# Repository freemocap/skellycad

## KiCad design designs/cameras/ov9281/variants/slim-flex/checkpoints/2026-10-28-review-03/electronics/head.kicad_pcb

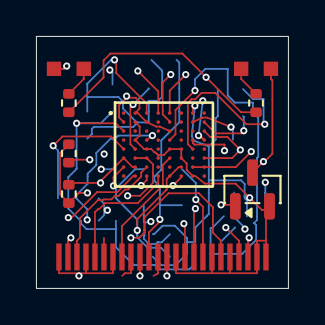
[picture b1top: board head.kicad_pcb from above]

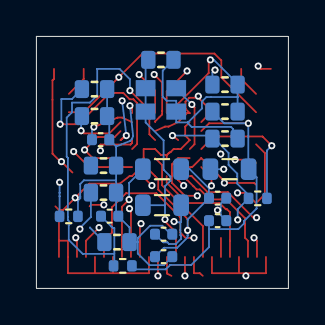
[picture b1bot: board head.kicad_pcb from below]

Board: 4 copper layers, 14.0 x 14.0 mm, 31 parts (22 on the bottom side), 30 nets.

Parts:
C7, C8, C10, C12, C13, C18, C19, C21, C33: C_1u_0603; C_0603_1608Metric
C9, C14, C15, C16, C17, C20: C_100n_6V3_0402; C_0402_1005Metric
D201, D202: AP1608F3C; Kingbright_AP1608F3C_R09
J201: SOLDER FLEX / 24 contacts; Flex_Solder_24_P0.5_R05
L1, L2, L3: MLP2012S3R3MT; L_0805_2012Metric
Q201: MMBT3904,215; SOT-23
R7, R8, R9: R_0R_0402; R_0402_1005Metric
R201, R202: 1k 1%; R_0402_1005Metric
R203: 2.2k 1%; R_0402_1005Metric
R204: 100k 1%; R_0402_1005Metric
U1: ImageSensor_OV9281; OV9281
Y1: SG-210STF 24.0000ML; Epson_SG210STF_2.5x2.0mm_R09

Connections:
+1V2: J201.17, L1.1
+1V8: C33.1, J201.11, L2.1, Y1.1, Y1.4
+2V8: J201.19, L3.1
+3V3: J201.21, R201.1, R202.1
/CAM_L_CLK_N: J201.5, U1.H4
/CAM_L_CLK_P: J201.6, U1.G4
/CAM_L_D0_N: J201.2, U1.H3
/CAM_L_D0_P: J201.3, U1.G3
/CAM_L_D1_N: J201.8, U1.F5
/CAM_L_D1_P: J201.9, U1.G5
/CAM_NRST_1V8: J201.15, U1.A5
/IR_A1: D201.2, R201.2
/IR_A2: D202.2, R202.2
/IR_BASE: Q201.1, R203.2, R204.1
/IR_K: D201.1, D202.1, Q201.3
/LED_PWM: J201.22, R203.1
/M1_AVDD: C18.1, C19.1, C20.1, L3.2, R9.2, U1.B8, U1.C1, U1.G7, U1.G8
/M1_CAM_SCL_1V8: J201.12, U1.E4
/M1_CAM_SDA_1V8: J201.13, U1.A4
/M1_DOVDD: C13.1, C15.1, C16.1, L2.2, R7.1, U1.B7, U1.D3, U1.H2, U1.H6
/M1_DVDD: C9.1, C12.1, C14.1, L1.2, U1.A2, U1.B1, U1.B3, U1.C5, U1.D8, U1.F2, U1.F3, U1.G1, U1.G6, U1.H5
/M1_MCLK: U1.E2, Y1.3
/M1_PVDD: C17.1, R9.1, U1.D5
/M1_SID: R7.2, R8.1, U1.E1
/M1_VH: C21.1, U1.E8
/M1_VN1: C7.1, U1.D7
/M1_VN2: C8.1, U1.E7
/M1_VN3: C10.1, U1.F7
/M1_VSYNC_1V8_M: J201.16, U1.B5
GND: C7.2, C8.2, C9.2, C10.2, C12.2, C13.2, C14.2, C15.2, C16.2, C17.2, C18.2, C19.2, C20.2, C21.2, C33.2, J201.1, J201.4, J201.7, J201.10, J201.14, J201.18, J201.20, J201.23, J201.24, Q201.2, R8.2, R204.2, U1.A3, U1.A7, U1.B2, U1.C8, U1.D2, U1.E3, U1.E5, U1.E6, U1.F1, U1.F4, U1.F6, U1.F8, U1.G2, U1.H7, Y1.2

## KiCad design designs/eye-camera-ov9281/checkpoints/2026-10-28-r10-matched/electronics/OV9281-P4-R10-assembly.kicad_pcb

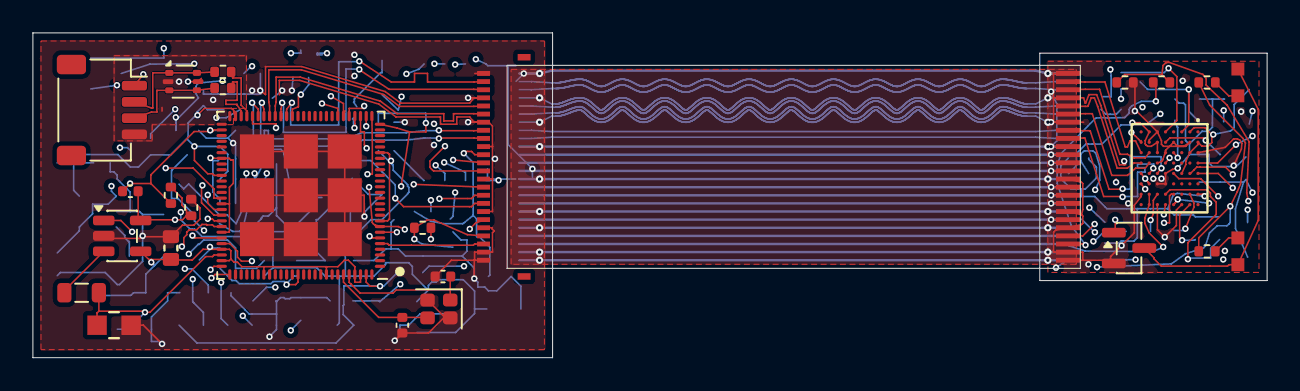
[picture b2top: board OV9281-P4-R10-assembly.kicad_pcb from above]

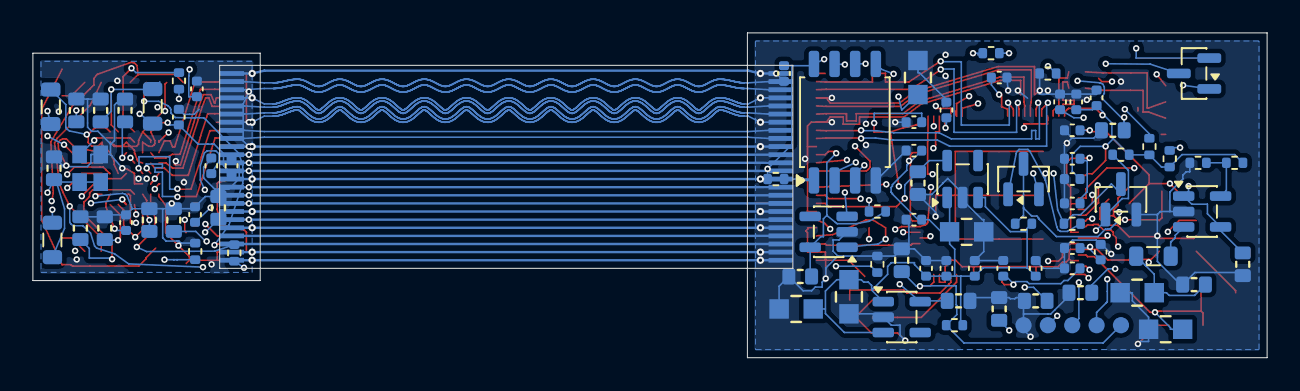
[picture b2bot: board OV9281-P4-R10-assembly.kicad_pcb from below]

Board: 6 copper layers, 76.0 x 20.0 mm, 110 parts (84 on the bottom side), 62 nets.

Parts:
C1, C2, C3: C_4u7_0805; C_0805_2012Metric
C4, C5, C6, C7, C8, C10, C12, C13, C18, C19, C21, C33: C_1u_0603; C_0603_1608Metric
C9, C14, C15, C16, C17, C20: C_100n_6V3_0402; C_0402_1005Metric
C101, C102: CL_TBD; C_0402_1005Metric
C103, C132, C135: 100n; C_0402_1005Metric
C104, C125, C126, C127, C133: 1u; C_0603_1608Metric
C105, C108, C136: 4.7u; C_0603_1608Metric
C106, C109: 22u; C_0805_2012Metric
C107: 22p; C_0402_1005Metric
C110: 100n / U101.9; C_0402_1005Metric
C111: 100n / U101.21; C_0402_1005Metric
C112: 100n / U101.26; C_0402_1005Metric
C113: 100n / U101.54; C_0402_1005Metric
C114: 100n / U101.62; C_0402_1005Metric
C115: 100n / U101.75; C_0402_1005Metric
C116: 100n / U101.76; C_0402_1005Metric
C117: 100n / U101.77; C_0402_1005Metric
C118: 100n / U101.85; C_0402_1005Metric
C119: 100n / U101.91; C_0402_1005Metric
C120: 100n / U101.96; C_0402_1005Metric
C121: 100n / U101.101; C_0402_1005Metric
C122: 100n / U101.102; C_0402_1005Metric
C123, C124: 10u; C_0805_2012Metric
C128: 100n / U101.30; C_0402_1005Metric
C129: 100n / U101.59; C_0402_1005Metric
C130: 100n / U101.67; C_0402_1005Metric
C131, C134: 10n; C_0402_1005Metric
D201, D202: AP1608F3C; Kingbright_AP1608F3C_R09
J101: USB / JST 4-contact candidate; JST_SH_SM04B-SRSS-TB_1x04-1MP_P1.00mm_Horizontal
J102: FH34SRJ-24S-0.5SH(99); Hirose_FH34SRJ_24S_0.5SH_R05
J103: PROGRAM / RESET pads; ProgrammingPads_5x1mm_P1.5mm
J201: SOLDER FLEX / 24 contacts; Flex_Solder_24_P0.5_R05
J301, J302: FLEX CONTACTS / B.Cu; Flex_Contacts_R05
L1, L2, L3: MLP2012S3R3MT; L_0805_2012Metric
L101, L102: 2.2u / Isat TBD; L_0805_2012Metric
Q101, Q102: BSS138; SOT-23
Q103: BSS138 / reset asserted HIGH; SOT-23
Q201: MMBT3904,215; SOT-23
R7, R8, R9: R_0R_0402; R_0402_1005Metric
R101, R102, R103, R104, R117, R118: 10k; R_0402_1005Metric
R105, R106: 499k; R_0402_1005Metric
R107: 453k; R_0402_1005Metric
R108, R116: 100k; R_0402_1005Metric
R109, R110: 0; R_0402_1005Metric
R111: 4.02k 1%; R_0402_1005Metric
R112, R113, R114, R115: 4.7k; R_0402_1005Metric
R201, R202: 1k 1%; R_0402_1005Metric
R203: 2.2k 1%; R_0402_1005Metric
R204: 100k 1%; R_0402_1005Metric
U1: ImageSensor_OV9281; OV9281
U5: TLV73318PDBVT; SOT-23-5
U6: TLV73312PDBVT; SOT-23-5
U7: TLV73328PDBVT; SOT-23-5
U101: ESP32-P4NRW16X / v3.x; ESP32-P4
U102: W25Q32JVSS (4 MB candidate); SOIC-8_5.3x5.3mm_P1.27mm
U103: TLV62569DBV / core; SOT-23-5
U104: TLV62569DBV / system; SOT-23-5
U105: USBLC6-2P6; SOT-666
Y1: SG-210STF 24.0000ML; Epson_SG210STF_2.5x2.0mm_R09
Y101: 40 MHz / CL TBD; Crystal_SMD_2016-4Pin_2.0x1.6mm

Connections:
+1V2: C6.1, J102.17, J201.17, J301.17, J302.17, L1.1, U6.5
+1V8: C5.1, C33.1, J102.11, J201.11, J301.11, J302.11, L2.1, Q101.1, Q102.1, R112.1, R114.1, R117.1, U5.5, Y1.1, Y1.4
+2V8: C4.1, J102.19, J201.19, J301.19, J302.19, L3.1, U7.5
+3V3: C1.1, C2.1, C3.1, C105.1, C109.1, C110.1, C111.1, C114.1, C115.1, C117.1, C118.1, C120.1, C121.1, C122.1, C123.1, C134.1, C135.1, C136.1, J102.21, J201.21, J301.21, J302.21, L102.2, R102.1, R103.1, R104.1, R107.1, R113.1, R115.1, R116.1, R201.1, R202.1, U5.1, U5.3, U6.1, U6.3, U7.1, U7.3, U101.9, U101.21, U101.51, U101.62, U101.75, U101.77, U101.85, U101.96, U101.101, U101.102, U103.4
/CAM_L_CLK_N: J102.5, J201.5, J301.5, J302.5, U1.H4, U101.45
/CAM_L_CLK_P: J102.6, J201.6, J301.6, J302.6, U1.G4, U101.44
/CAM_L_D0_N: J102.2, J201.2, J301.2, J302.2, U1.H3, U101.42
/CAM_L_D0_P: J102.3, J201.3, J301.3, J302.3, U1.G3, U101.43
/CAM_L_D1_N: J102.8, J201.8, J301.8, J302.8, U1.F5, U101.46
/CAM_L_D1_P: J102.9, J201.9, J301.9, J302.9, U1.G5, U101.47
/CAM_NRST_1V8: J102.15, J201.15, J301.15, J302.15, Q103.3, R117.2, U1.A5
/CAM_RESET_ASSERT: Q103.1, R116.2, U101.6
/CAM_SCL_3V3: Q101.3, R113.2, U101.7
/CAM_SDA_3V3: Q102.3, R115.2, U101.8
/FLASH_CLK: U101.32, U102.6
/FLASH_CS: R101.2, U101.27, U102.1
/FLASH_D: U101.33, U102.5
/FLASH_HOLD: U101.31, U102.7
/FLASH_Q: U101.28, U102.2
/FLASH_WP: U101.29, U102.3
/IR_A1: D201.2, R201.2
/IR_A2: D202.2, R202.2
/IR_BASE: Q201.1, R203.2, R204.1
/IR_K: D201.1, D202.1, Q201.3
/LED_PWM: J102.22, J201.22, J301.22, J302.22, R203.1, U101.5
/M1_AVDD: C18.1, C19.1, C20.1, L3.2, R9.2, U1.B8, U1.C1, U1.G7, U1.G8
/M1_CAM_SCL_1V8: J102.12, J201.12, J301.12, J302.12, Q101.2, R112.2, U1.E4
/M1_CAM_SDA_1V8: J102.13, J201.13, J301.13, J302.13, Q102.2, R114.2, U1.A4
/M1_DOVDD: C13.1, C15.1, C16.1, L2.2, R7.1, U1.B7, U1.D3, U1.H2, U1.H6
/M1_DVDD: C9.1, C12.1, C14.1, L1.2, U1.A2, U1.B1, U1.B3, U1.C5, U1.D8, U1.F2, U1.F3, U1.G1, U1.G6, U1.H5
/M1_MCLK: U1.E2, Y1.3
/M1_PVDD: C17.1, R9.1, U1.D5
/M1_SID: R7.2, R8.1, U1.E1
/M1_VH: C21.1, U1.E8
/M1_VN1: C7.1, U1.D7
/M1_VN2: C8.1, U1.E7
/M1_VN3: C10.1, U1.F7
/M1_VSYNC_1V8_M: J102.16, J201.16, J301.16, J302.16, R118.1, U1.B5
/P4_BOOT: J103.4, R103.2, U101.66
/P4_CSI_REXT: R111.1, U101.48
/P4_DOWNLOAD_ENABLE: R104.2, U101.68
/P4_EN: C104.1, J103.5, R102.2, U101.103
/P4_EN_DCDC: U101.79, U103.1
/P4_FB: C107.2, R105.2, R106.1, U101.78, U103.5
/P4_FLASH_VDD: C103.1, C125.1, C128.1, R101.1, U101.30, U101.71, U102.8
/P4_LDO4_UNUSED: C127.1, U101.74
/P4_MIPI_2V5: C131.1, C132.1, C133.1, U101.41, U101.73
/P4_PSRAM_VDD: C126.1, C129.1, C130.1, U101.59, U101.67, U101.72
/P4_SW: L101.1, U103.3
/P4_UART_RX: J103.3, U101.70
/P4_UART_TX: J103.2, U101.69
/P4_VDD_HP: C106.1, C107.1, C112.1, C113.1, C116.1, C119.1, C124.1, L101.2, R105.1, U101.26, U101.54, U101.76, U101.91
/P4_XTAL_N: C102.1, U101.99, Y101.3
/P4_XTAL_P: C101.1, U101.100, Y101.1
/SYS_FB: R107.2, R108.1, U104.5
/SYS_SW: L102.1, U104.3
/USB_DM: J101.2, R109.1, U105.1, U105.6
/USB_DM_CHIP: R109.2, U101.49
/USB_DP: J101.3, R110.1, U105.3, U105.4
/USB_DP_CHIP: R110.2, U101.50
/USB_VBUS: C108.1, J101.1, U104.1, U104.4, U105.5
GND: C1.2, C2.2, C3.2, C4.2, C5.2, C6.2, C7.2, C8.2, C9.2, C10.2, C12.2, C13.2, C14.2, C15.2, C16.2, C17.2, C18.2, C19.2, C20.2, C21.2, C33.2, C101.2, C102.2, C103.2, C104.2, C105.2, C106.2, C108.2, C109.2, C110.2, C111.2, C112.2, C113.2, C114.2, C115.2, C116.2, C117.2, C118.2, C119.2, C120.2, C121.2, C122.2, C123.2, C124.2, C125.2, C126.2, C127.2, C128.2, C129.2, C130.2, C131.2, C132.2, C133.2, C134.2, C135.2, C136.2, J101.4, J102.1, J102.4, J102.7, J102.10, J102.14, J102.18, J102.20, J102.23, J102.24, J103.1, J201.1, J201.4, J201.7, J201.10, J201.14, J201.18, J201.20, J201.23, J201.24, J301.1, J301.4, J301.7, J301.10, J301.14, J301.18, J301.20, J301.23, J301.24, J302.1, J302.4, J302.7, J302.10, J302.14, J302.18, J302.20, J302.23, J302.24, Q103.2, Q201.2, R8.2, R106.2, R108.2, R111.2, R118.2, R204.2, U1.A3, U1.A7, U1.B2, U1.C8, U1.D2, U1.E3, U1.E5, U1.E6, U1.F1, U1.F4, U1.F6, U1.F8, U1.G2, U1.H7, U5.2, U6.2, U7.2, U101.105, U102.4, U103.2, U104.2, U105.2, Y1.2, Y101.2, Y101.4

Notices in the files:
parts and their libraries:
License: Apache-2.0
